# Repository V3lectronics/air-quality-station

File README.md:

# Air quality station
V Electronics Air Quality Station design files & code, everything is open source and can be modified easily by the user. The device measures air pollution, temperature and humidity.

> [!NOTE]
> This is a work in progress!

# Specification:
Measurement range
| Air pollution | Temperature | Humidity |
| --------------- | --------------- | --------------- |
| todo | Item2.1   -40°C to +80°C ±0.5°C  | 0% to 99,9%RH ±3RH (at 25°C) |

- USB C power/programming (MCU fully unlocked)
- 2x16 LCD display + vertical bar LCD color display 
- No battery (a powerbank can be used)
- Not waterproof

# Components list

- Seeed Studio XIAO ESP32C3 [link](https://wiki.seeedstudio.com/XIAO_ESP32C3_Getting_Started/)
<div style='text-align: center;'> 
  
</div> 

- GRAVITY PM2.5 air quality sensor [link](https://www.dfrobot.com/product-2439.html)
> [!TODO] //find cheaper for example https://www.dfrobot.com/product-2526.html
<div style='text-align: center;'> 

</div> 
> [!NOTE]
> Other sensors can be used as alternatives if you need more precise measurements.

- LCD Display + I2C adapter [link]()
> [!TODO] //find suitable option
<div style='text-align: center;'> 
  
</div> 

- Vertical bar vertical indicator [link](https://www.digikey.pl/en/products/detail/inolux/INBD-T11020-YGNB/16964097)
<div style='text-align: center;'> 
  
</div> 

- AM2320 temperature & humidity sensor [link](https://www.digikey.pl/pl/products/detail/pimoroni-ltd/COM1700/8126047)
<div style='text-align: center;'> 
  
</div> 

> [!NOTE]
> DHT12 can be used as a slightly cheaper alternative compromising accuracy and measurement range.

- On/Off switch [link](https://www.digikey.pl/en/products/detail/adam-tech/SW-T3-1A-A-A3-S1/15284460)
<div style='text-align: center;'> 
  
</div> 

- PS1240P02BT buzzer [link](https://www.digikey.pl/en/products/detail/tdk-corporation/PS1240P02BT/935924)
<div style='text-align: center;'> 
</div> 

- 2N3904 driving transistor [link](https://www.digikey.pl/en/products/detail/shenzhen-slkormicro-semicon-co-ltd/2N3904/26371060)
<div style='text-align: center;'> 
</div> 

# TODO

- add test points
- add drill holes to mount sensor to PCB
- add gpio outputs for extra stuff
- add led at analog output
- add made in kicad (copy from cm5 io board)
- wifi/bluetooth connectivity???

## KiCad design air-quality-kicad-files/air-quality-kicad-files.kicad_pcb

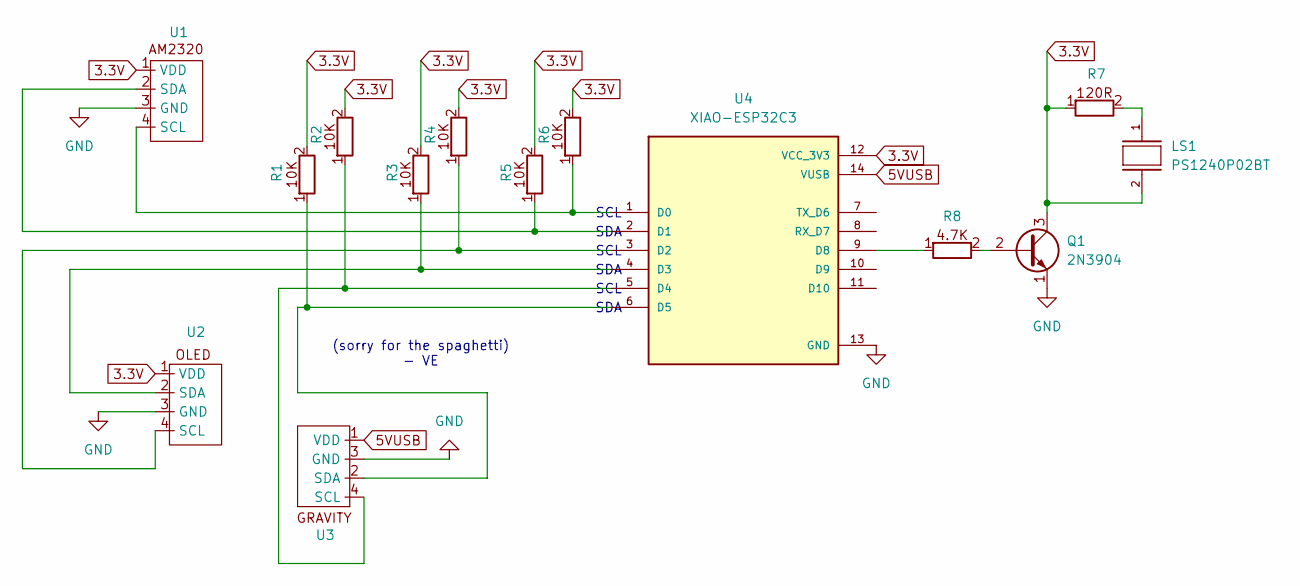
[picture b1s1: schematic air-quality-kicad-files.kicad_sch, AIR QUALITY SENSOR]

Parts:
LS1: PS1240P02BT; buzzer-XDCR_PS1240P02BT
Q1: 2N3904; TO-92_Inline
R1, R2, R3, R4, R5, R6: 10kOhm-pullup
R7: 120R
R8: 4-7K
U1: AM2320
U2: OLED
U3: Gravity
U4: XIAO-ESP32C3; PARTREV 23/05/2022

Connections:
3.3V: LS1.2, Q1.3 (C), R1.2, R2.2, R3.2, R4.2, R5.2, R6.2, R7.1, U1.1 (VDD), U2.1 (VDD), U4.12 (VCC_3V3)
5VUSB: U3.1 (VDD), U4.14 (VUSB)
GND: Q1.1 (E), U1.3 (GND), U2.3 (GND), U3.3 (GND), U4.13 (GND)
unnamed: LS1.1, R7.2
unnamed: Q1.2 (B), R8.2
unnamed: R6.1, U1.4 (SCL), U4.1 (D0)
unnamed: R5.1, U1.2 (SDA), U4.2 (D1)
unnamed: R4.1, U2.4 (SCL), U4.3 (D2)
unnamed: R3.1, U2.2 (SDA), U4.4 (D3)
unnamed: R2.1, U3.4 (SCL), U4.5 (D4)
unnamed: R1.1, U3.2 (SDA), U4.6 (D5)
unnamed: R8.1, U4.9 (D8)

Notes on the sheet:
(sorry for the spaghetti) - VE
SDA
SCL

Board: 2 copper layers, 14 parts (0 on the bottom side), 12 nets, no tracks yet.

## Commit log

2025-03-28 add list and images
2025-03-28 init kicad files
2025-03-31 update kicad files as of livestream 1
2025-03-31 change images size and fix them
2025-05-20 added resistors, buzzer circuit, holes, cleaned up files
2025-05-20 fix images, layout
